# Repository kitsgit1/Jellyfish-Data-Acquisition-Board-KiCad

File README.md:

# Jellyfish Data Acquisition Board KiCad PCB Files
This is one of 3 repositories related to the Jellyfish Data Acquisition project. The goal is to build the hardware for a noninvasive electrode array capable of detecting neronal activity of small jellyfish, the firmware to digitize the signals and control the multiplexing of each pixel, and the software to control the system and graph the data.
| **Hardware** <br/> (You Are Here)      | Firmware      | Software |
| ------------- | ------------- | ------------- |
| <br/>https://github.com/kitsgit1/Jellyfish-Data-Acquisition-Board-KiCad |  <br/>https://github.com/kitsgit1/Jellyfish-Data-Acquisition-STM32 |  <br/>https://github.com/kitsgit1/Jellyfish-Data-Display-GUI |

# Hardware Documentation - Rev A
There are two boards that make up the assembly: the Electrode board and the Digitizer board.
## Jellyfish Electrode Board
The electrode board is responsible for interfacing with the jellyfish and multiplexing all pixels down to one wire using low charge-injection analog mux's. There is an optional path for a front-end buffer amplifier (non-inverting x2 gain for Rf = Rg). I/O consists of the Guard signal which drives the saltwater bath to the same potential as the op-amp reference voltage, the digital I/O to control the shift registers that select the correct pixel through setting all the multiplexers, and the single analog switched electrode signal.

## Jellyfish Digitizer Board
The digitizer board further amplifies the tiny signal from the electrode board into something the STM32's 10MHz/12-bit ADC can handle. The STM32 is also responsible for collecting, storing, and sending data to either the PC over USB or to an SD card.

Details to come...

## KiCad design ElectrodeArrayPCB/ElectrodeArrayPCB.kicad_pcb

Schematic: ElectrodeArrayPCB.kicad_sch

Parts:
BT1: XT30PW-M30.G.Y; AMASS_XT30PW-M_1x02_P2.50mm_Horizontal; LCSC C431092
C1, C6, C7, C8, C9, C13, C14, C15, C18, C20, C22, C23, C24, C25, C30, C36, C38, C39, C41, C42, C43, C46, C51, C52, C53, C54, C55, C56, C59, C63, C64, C68, C70, C72, C73: 100nF; C_0402; Voltage Rated 50V; Tolerance ±10%; Part CL05B104KB54PNC; LCSC C307331
C2, C4, C5, C17, C21, C26, C29, C32, C76: 10uF; C_0805; Voltage Rated 25V; Tolerance ±10%; Part CL21A106KAYNNNE; LCSC C15850
C3, C27, C58, C81: 4.7uF; C_0402; Voltage Rated 10V; Tolerance ±20%; Part CL05A475MP5NRNC; LCSC C23733
C10, C11, C12, C16, C28, C67, C69, C71, C77, C79, C80: 47uF; C_1206; Voltage Rated 10V; Tolerance ±20%; Part CL31A476MPHNNNE; LCSC C96123
C19, C44, C45, C78: 10pF; C_0402; Voltage Rated 50V; Tolerance ±5%; Part CL05C100JB5NNNC; LCSC C32949
C31, C37, C40, C57, C60: 1uF; C_0402; Voltage Rated 25V; Tolerance ±10%; Part CL05A105KA5NQNC; LCSC C52923
C61, C62: 2.2uF; C_0603; Voltage Rated 16V; Tolerance ±10%; Part CL10A225KO8NNNC; LCSC C23630
C65, C66: 470pF; C_0402; Voltage Rated 50V; Tolerance ±10%; Part 0402B471K500NT; LCSC C1537
C74, C75: 20pF; C_0402; Voltage Rated 50V; Tolerance ±5%; Part 0402CG200J500NT; LCSC C1554
D1, D2, D3: Red; D_0603; Part KT-0603R; LCSC C2286
FB1, FB2, FB3, FB4: FB_0805; Current Rating 800mA; Tolerance ±25%; Part GZ2012D101TF; LCSC C1015
J1: HX PZ1.27-2x5P TP; PinHeader_2x05_P1.27mm_Vertical_SMD
J2, J10: Conn_01x10_Pin; Electrode_Line_8_Test
J3, J7, J8, J9, J11: KH-SMAK-SMT; SMA_Wurth_60312102114405_Vertical
J4: 1040310811; microSD_HC_Molex_104031-0811; LCSC C585350
J5: Conn_ARM_SWD_TagConnect_TC2030; Tag-Connect_TC2030-IDC-FP_2x03_P1.27mm_Vertical
J6: Connector, USB-TYPE-C-16P; TYPE-C-SMD_HX-TYPE-C-16PIN; LCSC C2927039
J12: 2.54-1*3PPin; PinHeader_1x03_P2.54mm_Vertical; LCSC C49257
P1, P2: Jumper Shunt; LCSC C2758458
R1, R7, R19, R22, R32, R36, R47, R89, R97, R98, R99, R105: 1kΩ; R_0402; Overload Voltage (Max) 50V; Tolerance ±1%; Part 0402WGF1001TCE; LCSC C11702
R2, R5, R29, R49, R54, R119: 270kΩ; R_0603; Overload Voltage (Max) 75V; Tolerance ±1%; Part 0603WAF2703T5E; LCSC C22965
R3, R42, R46, R90, R91, R118: 100kΩ; R_0402; Overload Voltage (Max) 50V; Tolerance ±1%; Part 0402WGF1003TCE; LCSC C25741
R4, R34, R103: 10kΩ; R_0402; Overload Voltage (Max) 50V; Tolerance ±1%; Part 0402WGF1002TCE; LCSC C25744
R6, R25, R50: 12kΩ; R_0402; Overload Voltage (Max) 50V; Tolerance ±1%; Part 0402WGF1202TCE; LCSC C25752
R8, R51, R102: 0Ω; R_1206; Overload Voltage (Max) 200V; Tolerance ±1%; Part 1206W4F0000T5E; LCSC C17888
R9, R48: 22kΩ; R_0402; Overload Voltage (Max) 50V; Tolerance ±1%; Part 0402WGF2202TCE; LCSC C25768
R10, R11, R17, R18, R20, R21, R23, R27, R28, R30, R31, R35, R37, R44, R45, R53, R55, R58, R71, R78, R85, R86, R87, R88, R92, R95, R107, R109, R110, R111, R113, R114, R115, R120: 0Ω; R_0402; Overload Voltage (Max) 50V; Tolerance ±1%; Part 0402WGF0000TCE; LCSC C17168
R12: 33kΩ; R_0402; Overload Voltage (Max) 50V; Tolerance ±1%; Part 0402WGF3302TCE; LCSC C25779
R13, R100, R106: 49.9Ω; R_0402; Overload Voltage (Max) 50V; Tolerance ±1%; Part 0402WGF499JTCE; LCSC C25120
R14, R26: 100Ω; R_0402; Overload Voltage (Max) 50V; Tolerance ±1%; Part 0402WGF1000TCE; LCSC C25076
R15, R16, R24, R43, R52, R56, R57, R96, R101, R116, R117: 0Ω; R_0402; Overload Voltage (Max) 50V; Tolerance ±1%; Part 0402WGF0000TCE; LCSC C17168; not fitted
R33, R39: 470kΩ; R_0402; Overload Voltage (Max) 50V; Tolerance ±1%; Part 0402WGF4703TCE; LCSC C25790
R38: 220kΩ; R_0402; Overload Voltage (Max) 50V; Tolerance ±1%; Part 0402WGF2203TCE; LCSC C25767
R40, R93: 1MΩ; R_0402; Overload Voltage (Max) 50V; Tolerance ±1%; Part 0402WGF1004TCE; LCSC C26083
R41, R59, R60, R61, R62, R63, R64: 47kΩ; R_0402; Overload Voltage (Max) 50V; Tolerance ±1%; Part 0402WGF4702TCE; LCSC C25792
R65, R66, R67, R68, R69, R70, R72, R73, R74, R75, R76, R77, R79, R80, R81, R82, R83, R84: 10Ω; R_0402; Overload Voltage (Max) 50V; Tolerance ±1%; Part 0402WGF100JTCE; LCSC C25077
R94, R104: 5.1kΩ; R_0603; Overload Voltage (Max) 75V; Tolerance ±1%; Part 0603WAF5101T5E; LCSC C23186
R108: 1Ω; R_0402; Overload Voltage (Max) 50V; Tolerance ±1%; Part 0402WGF100KTCE; LCSC C25086
R112: 0Ω; R_0805; Overload Voltage (Max) 150V; Tolerance ±1%; Part 0805W8F0000T5E; LCSC C17477
S1: Tactile Button, 160gf; SW_TS-1088-AR02016; Voltage Rating (Dc) 12V; Part TS-1088-AR02016; LCSC C720477
TP1, TP2, TP5, TP6, TP7: RH-5000; TestPoint_Loop_D2.54mm_Drill1.5mm_Beaded; LCSC C5277086
TP3: RH-5001; TestPoint_Loop_D2.54mm_Drill1.5mm_Beaded
TP4, TP8, TP9, TP10, TP11, TP12, TP13, TP14: RH-5001; TestPoint_Loop_D2.54mm_Drill1.5mm_Beaded; LCSC C5199801
U1, U4, U28: TPS7A9401DSCR; VSON-10-1EP_3x3mm_P0.5mm_EP1.65x2.4mm_ThermalVias; LCSC C5220127
U2, U3: HX PZ2.54-3x3P ZZ; PinHeader_03x03_0.1in; LCSC C32713290
U5: 74HC4067PW,118; SSOP-24_5.3x8.2mm_P0.65mm; LCSC C179326
U9: CJ431; SOT-23-3_L2.9-W1.6-P1.90-LS2.8-BR; Output Voltage 2.5V~36V; Tolerance ±0.5%; Part CJ431; LCSC C3113
U10: REF2033AIDDCR; SOT-23-5; LCSC C440747
U11: LMP7721; SOIC-8_3.9x4.9mm_P1.27mm
U12: LMP7715; SOT-23-5
U14: ADA4940-1ACPZ-R2; LFCSP-16-1EP_3x3mm_P0.5mm_EP1.3x1.3mm_ThermalVias; LCSC C654337
U15: STM32H7B0VBT6; LQFP-100_14x14mm_P0.5mm; LCSC C730227
U16, U17: OPA847IDBVR; SOT-23-6; LCSC C160422
U19: TMUX1108PW; TSSOP-16_4.4x5mm_P0.65mm
U24, U25: APS6404L-3SQR-SN; SOIC-8_3.9x4.9mm_P1.27mm; LCSC C5333729
U27: REF5025AIDR; SOIC-8_L4.9-W3.9-P1.27-LS6.0-BL
X1: X322516MLB4SI; OSC-SMD_4P-L3.2-W2.5-BL; Frequency Tolerance ±10ppm; Part X322516MLB4SI; LCSC C13738

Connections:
+3.3V: R8.2, R52.2, R112.1
+3.3VA: FB2.2, R51.2
+5V: C9.1, C16.1, R14.2, R18.1, R19.1, R27.2, R30.2, R37.2, R44.1, R45.1, R85.2, R102.2, R109.2, U3.1
/MCU_VDD33: C51.1, C52.1, C53.1, C54.1, C55.1, C56.1, C57.1, C58.1, R58.1, R71.1, R78.1, R89.1, R92.2, R112.2, U15.6 (VBAT), U15.11 (VDD), U15.27 (VDD), U15.50 (VDD), U15.75 (VDD), U15.100 (VDD)
/PA11_USB_DM: J6.A7 (D-), J6.B7 (D-), U15.70 (PA11)
/PA12_USB_DP: J6.A6 (D+), J6.B6 (D+), U15.71 (PA12)
/USART1_RX: J12.2, U15.54 (PB15)
/USART1_TX: J12.1, U15.53 (PB14)
/amp_inverting_input: R34.1, U12.3 (+)
/battery: BT1.1 (+), C20.1, C21.1, FB1.1, FB3.1, FB4.1
/grd_drv_out: R26.2, U12.1, U12.4 (-)
/ldo_3v3: C10.1, C17.1, C18.1, R5.2, R8.1, TP2.1, U1.8 (SNS), U1.9 (OUT), U1.10 (OUT)
/ldo_3v3A: C28.1, C29.1, C30.1, R49.2, R51.1, TP7.1, U4.8 (SNS), U4.9 (OUT), U4.10 (OUT)
/ldo_5v: C4.1, C7.1, C80.1, R54.2, R102.1, TP1.1, U28.8 (SNS), U28.9 (OUT), U28.10 (OUT)
/vbat_post_fb5: C5.1, C6.1, FB3.2, R1.2, R119.1, U28.1 (IN), U28.2 (IN)
/vbat_post_fb33: C1.1, C2.1, FB1.2, R2.1, R7.1, U1.1 (IN), U1.2 (IN)
/vbat_post_fb33A: C22.1, C26.1, FB4.2, R29.1, R47.1, U4.1 (IN), U4.2 (IN)
ADC_N: R100.2, R114.1
ADC_P: R106.2, R113.1
GND: BT1.2 (-), C1.2, C2.2, C3.2, C4.2, C5.2, C6.2, C7.2, C8.2, C9.2, C10.2, C11.2, C12.2, C13.2, C14.2, C15.2, C16.2, C17.2, C18.2, C19.1, C20.2, C21.2, C22.2, C23.2, C24.2, C25.2, C26.2, C27.2, C28.2, C29.2, C30.2, C31.2, C32.2, C36.2, C37.2, C38.2, C39.2, C40.2, C41.2, C42.1, C43.2, C44.2, C45.1, C46.2, C51.2, C52.2, C53.2, C54.2, C55.2, C56.2, C57.2, C58.2, C59.2, C60.2, C61.2, C62.2, C63.2, C64.2, C68.2, C69.2, C70.2, C71.2, C72.2, C73.2, C76.2, C77.2, C79.2, C80.2, C81.2, J3.2 (Ext), J4.6 (VSS), J4.9 (SHIELD), J5.5 (GND), J6.A12B1 (GND), J6.B12A1 (GND), J7.2 (Ext), J8.2 (Ext), J9.2 (Ext), J11.2 (Ext), J12.3, R3.2, R6.2, R9.2, R12.2, R13.2, R15.2, R17.1, R24.1, R25.2, R46.2, R48.2, R50.2, R93.2, R94.2, R104.2, R107.2, R108.2, R116.1, R117.2, R118.2, S1.1 (A), TP3.1, TP4.1, TP8.1, TP9.1, TP10.1, TP11.1, U1.6 (GND), U1.11 (EPAD), U2.1, U2.3, U2.7, U2.9, U3.2, U3.4, U3.5, U4.6 (GND), U4.11 (EPAD), U5.12 (GND), U5.13 (S3), U5.15 (~E), U9.3 (AN), U10.2 (GND), U11.3 (V-), U12.2 (V-), U14.13 (-Vs), U14.14 (-Vs), U14.15 (-Vs), U14.16 (-Vs), U14.17 (EP), U15.10 (VSS), U15.19 (VSSA), U15.26 (VSS), U15.49 (VSS), U15.74 (VSS), U15.99 (VSS), U16.2 (V-), U17.2 (V-), U19.3 (VSS), U19.14 (GND), U24.4 (VSS), U25.4 (VSS), U27.4 (GND), U28.6 (GND), U28.11 (EPAD), X1.2 (GND), X1.4 (GND)
unnamed: C14.1, C67.1, P2.2, R23.1, R53.1, R101.2
unnamed: C41.1, C76.1, R85.1, R95.2, U14.5 (+Vs), U14.6 (+Vs), U14.7 (+Vs), U14.8 (+Vs)
unnamed: C61.1, C62.1, C63.1, C64.1, U15.48 (VCAP), U15.73 (VCAP)
unnamed: C65.2, C66.1, R107.1
unnamed: C67.2, R108.1
unnamed: D1.2, R1.1
unnamed: D2.2, R7.2
unnamed: D3.2, R47.2
unnamed: J1.1, R40.2, R43.2
unnamed: J1.3, R39.2
unnamed: J1.5, R38.2
unnamed: J1.7, R42.2
unnamed: J1.9, P1.1, R41.2
unnamed: J1.2, J1.4, J1.6, J1.8, J1.10, P1.2, R43.1, R55.1, R56.1, R105.1
unnamed: J2.1, U5.9 (I0)
unnamed: J2.2, U5.8 (I1)
unnamed: J2.3, U5.7 (I2)
unnamed: J2.4, U5.6 (I3)
unnamed: J2.5, U5.5 (I4)
unnamed: J2.6, U5.4 (I5)
unnamed: J2.7, U5.3 (I6)
unnamed: J2.8, U5.2 (I7)
unnamed: J2.9, J8.1 (In)
unnamed: J3.1 (In), R20.1
unnamed: J4.5 (CLK), R64.2, R69.2
unnamed: J4.3 (CMD), R63.2, R70.2
unnamed: J4.7 (DAT0), R60.2, R65.2
unnamed: J4.8 (DAT1), R61.2, R66.2
unnamed: J4.1 (DAT2), R59.2, R67.2
unnamed: J4.2 (DAT3/CD), R62.2, R68.2
unnamed: C36.1, J4.4 (VDD), R58.2, R59.1, R60.1, R61.1, R62.1, R63.1, R64.1
unnamed: J5.4 (SWCLK), R87.1
unnamed: J5.2 (SWDIO), R88.2
unnamed: J5.1 (VCC), R91.1, R92.1
unnamed: J5.3 (~RESET), R86.1
unnamed: J6.A5 (CC1), R104.1
unnamed: J6.B5 (CC2), R94.1
unnamed: C46.1, J6.S1 (SHIELD), R93.1
unnamed: J6.A9B4 (VBUS), J6.B9A4 (VBUS), R96.1
unnamed: J7.1 (In), R120.2
unnamed: C19.2, J9.1 (In), R10.2, R11.2
unnamed: J10.1, U19.4 (S1)
unnamed: J10.2, U19.5 (S2)
unnamed: J10.3, U19.6 (S3)
unnamed: J10.4, U19.7 (S4)
unnamed: J10.5, U19.9 (S8)
unnamed: J10.6, U19.10 (S7)
unnamed: J10.7, U19.11 (S6)
unnamed: J10.8, U19.12 (S5)
unnamed: J2.10, J10.9
unnamed: J10.10, R13.1
unnamed: J11.1 (In), R28.2
unnamed: R21.2, U2.5
unnamed: R28.1, R55.2, U17.1
unnamed: R56.2, R57.1
unnamed: R17.2, R52.1, R103.1
unnamed: R33.2, R35.2, R57.2, R115.1
unnamed: R115.2, U16.1
unnamed: C42.2, R90.1, S1.2 (B)
unnamed: R2.2, R3.1, U1.3 (EN_UV)
unnamed: R5.1, R6.1, U1.5 (FB_PG)
unnamed: C3.1, R9.1, U1.7 (NR/SS)
unnamed: D2.1, U1.4 (PG)
unnamed: R29.2, R46.1, U4.3 (EN_UV)
unnamed: R49.1, R50.1, U4.5 (FB_PG)
unnamed: C27.1, R48.1, U4.7 (NR/SS)
unnamed: D3.1, U4.4 (PG)
unnamed: R10.1, U5.1 (COM)
unnamed: C8.1, R44.2, U5.24 (VCC)
unnamed: R16.1, R19.2, R101.1, U9.2 (CAT)
unnamed: R15.1, R16.2, U9.1 (REF)
unnamed: C70.1, C71.1, R109.1, U10.3 (EN), U10.4 (IN)
unnamed: C72.1, R110.1, U10.1 (Vbias)
unnamed: C73.1, R111.1, U10.5 (Vref)
unnamed: R20.2, U11.1 (IN+)
unnamed: C78.1, R4.1, R22.1, R34.2, U11.8 (IN-)
unnamed: C11.1, C12.1, C13.1, R27.1, U11.6 (V+)
unnamed: C78.2, R4.2, R31.2, U11.4 (Vout)
unnamed: C15.1, C77.1, C79.1, R14.1, U12.5 (V+)
unnamed: C74.2, R99.2, U14.4 (+FB)
unnamed: C75.1, R97.1, R105.2, U14.2 (+IN)
unnamed: R113.2, U14.10 (+OUT)
unnamed: C75.2, R97.2, U14.1 (-FB)
unnamed: C74.1, R98.2, R99.1, U14.3 (-IN)
unnamed: R114.2, U14.11 (-OUT)
unnamed: R110.2, U14.9 (VOCM)
unnamed: R95.1, U14.12 (~DISABLE)
unnamed: R103.2, U15.94 (BOOT0)
unnamed: R96.2, U15.68 (PA9)
unnamed: R88.1, R91.2, U15.72 (PA13)
unnamed: R87.2, U15.76 (PA14)
unnamed: C65.1, R100.1, U15.17 (PC2_C)
unnamed: C66.2, R106.1, U15.18 (PC3_C)
unnamed: R65.1, U15.65 (PC8)
unnamed: R66.1, U15.66 (PC9)
unnamed: R67.1, U15.78 (PC10)
unnamed: R68.1, U15.79 (PC11)
unnamed: R69.1, U15.80 (PC12)
unnamed: R81.1, U15.58 (PD11)
unnamed: R82.1, U15.59 (PD12)
unnamed: R84.1, U15.60 (PD13)
unnamed: R73.2, U15.37 (PE7)
unnamed: R74.2, U15.38 (PE8)
unnamed: R75.2, U15.39 (PE9)
unnamed: R76.2, U15.40 (PE10)
unnamed: R72.1, R79.1, U15.41 (PE11)
unnamed: C45.2, U15.12 (PH0), X1.3 (OSC)
unnamed: C44.1, U15.13 (PH1), X1.1 (OSC)
unnamed: C59.1, C60.1, FB2.1, U15.21 (VDDA)
unnamed: R21.1, R31.1, R120.1, U16.3 (+)
unnamed: R32.1, R33.1, U16.4 (-)
unnamed: C23.1, R30.1, U16.6 (V+)
unnamed: R116.2, U16.5 (~DIS)
unnamed: R35.1, U17.3 (+)
unnamed: R36.1, R38.1, R39.1, R40.1, R41.1, R42.1, U17.4 (-)
unnamed: C24.1, R37.1, U17.6 (V+)
unnamed: R117.1, U17.5 (~DIS)
unnamed: R11.1, U19.8 (D)
unnamed: C25.1, R45.2, U19.2 (EN), U19.13 (VDD)
unnamed: R77.2, U24.6 (SCLK)
unnamed: R75.1, U24.3 (SIO2)
unnamed: R76.1, U24.7 (SIO3)
unnamed: R73.1, U24.5 (SI/SIO0)
unnamed: R74.1, U24.2 (SO/SIO1)
unnamed: C37.1, C38.1, R71.2, U24.8 (VDD)
unnamed: R72.2, U24.1 (~CE)
unnamed: R80.1, U25.6 (SCLK)
unnamed: R83.2, U25.3 (SIO2)
unnamed: R84.2, U25.7 (SIO3)
unnamed: R81.2, U25.5 (SI/SIO0)
unnamed: R82.2, U25.2 (SO/SIO1)
unnamed: C39.1, C40.1, R78.2, U25.8 (VDD)
unnamed: R79.2, U25.1 (~CE)
unnamed: C31.1, C32.1, U27.5 (Trim/NR)
unnamed: C68.1, C69.1, R18.2, U27.2 (Vin)
unnamed: P2.1, R53.2, U27.6 (Vout)
unnamed: R118.1, R119.2, U28.3 (EN_UV)
unnamed: R25.1, R54.1, U28.5 (FB_PG)
unnamed: C81.1, R12.1, U28.7 (NR/SS)
unnamed: D1.1, U28.4 (PG)
PA7_OCTASPI_P1_IO2: R83.1, U15.31 (PA7)
PB2_OCTASPI_P1_CLK: R77.1, R80.2, U15.36 (PB2)
PD2_SDMMC1_CMD: R70.1, U15.83 (PD2)
STM32_RSTn: C43.1, R86.2, R89.2, R90.2, U15.14 (NRST)
Shift_OEb: U3.3, U15.28 (PA4)
Shift_RCLK: U3.6, U15.29 (PA5)
Shift_SER: U3.7, U15.33 (PC5)
Shift_SRCLK: U3.9, U15.32 (PC4)
Shift_SRCLRb: U3.8, U15.30 (PA6)
VCM_Guard_2.5V: R22.2, R23.2, R24.2, R32.2, R36.2, R98.1, TP5.1
Vref: R111.2, U15.20 (VREF+)
guard_ring: R26.1, TP6.1, U2.2, U2.4, U2.6, U2.8, U11.2 (GRD), U11.7 (GRD)
s0: TP14.1, U5.10 (S0), U15.1 (PE2), U19.1 (A0)
s1: TP13.1, U5.11 (S1), U15.2 (PE3), U19.16 (A1)
s2: TP12.1, U5.14 (S2), U15.3 (PE4), U19.15 (A2)

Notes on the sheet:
VCM=2.5V here
Alternate ram possibilities: APS12808L-3OBM-BA (128Mb OSPI, mouser) S70KL1281 (128Mb hyperam/OSPI, obsolete) W956A8MBYA5I (64Mb, LCSC stock, hyperbus) S66/67WVO32M8DALL/BLL (256Mb, OSPI)
16MHz
1.65V CM
1ms per AP spike (really 2-10ms) 20 points per spike -> 50us per sample -> 20kHz sample rate. 64 electrodes -> 1.28MHz sample rate. 4096 electrodes -> 81.92MHz sample rate, single CH. For now, pick ADC for 2MHz. High bit count.
DS Table 23

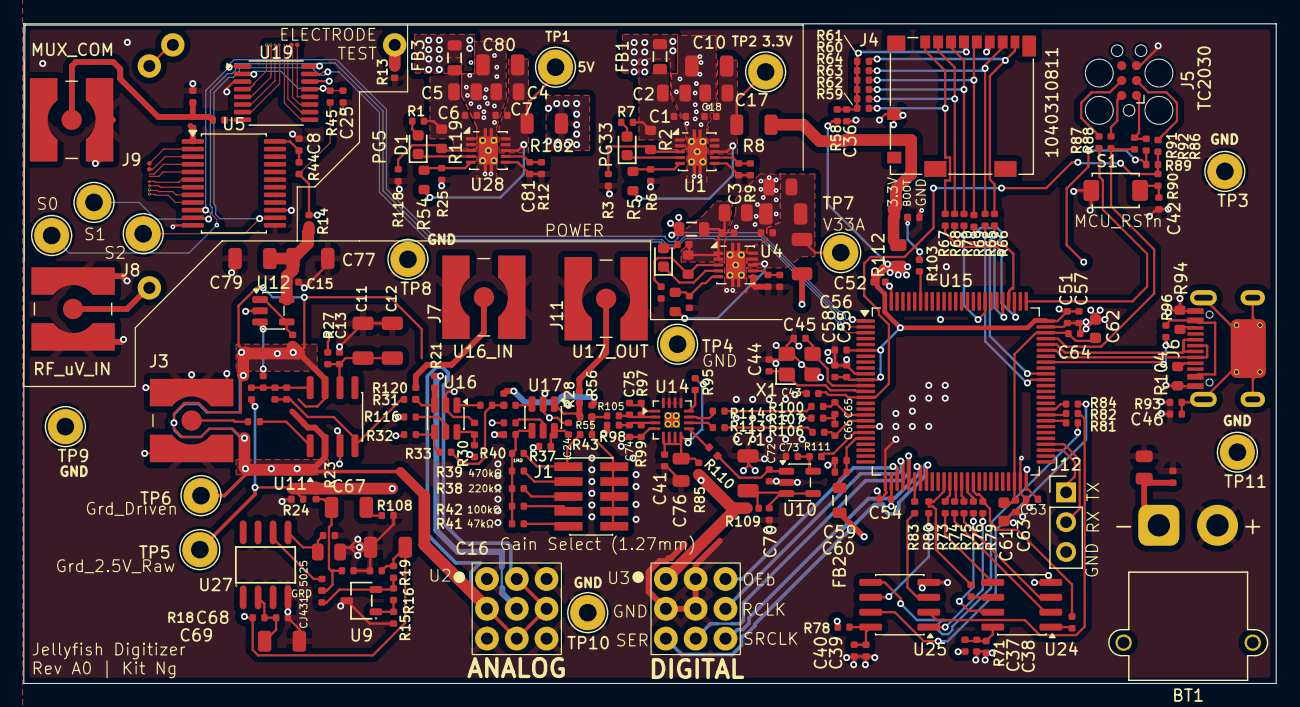
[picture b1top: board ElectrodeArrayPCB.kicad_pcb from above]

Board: 4 copper layers, 106.7 x 56.2 mm, 248 parts (0 on the bottom side), 175 nets.

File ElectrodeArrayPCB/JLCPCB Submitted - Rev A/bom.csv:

Designator,Footprint,Quantity,Value,LCSC Part #
BT1,AMASS_XT30PW-M_1x02_P2.50mm_Horizontal,1,XT30PW-M30.G.Y,C431092
"C1, C13, C14, C15, C18, C20, C22, C23, C24, C25, C30, C36, C38, C39, C41, C42, C43, C46, C51, C52, C53, C54, C55, C56, C59, C6, C63, C64, C68, C7, C70, C72, C73, C8, C9",C_0402,35,100nF,C307331
"C10, C11, C12, C16, C28, C67, C69, C71, C77, C79, C80",C_1206,11,47uF,C96123
"C17, C2, C21, C26, C29, C32, C4, C5, C76",C_0805,9,10uF,C15850
"C19, C44, C45, C78",C_0402,4,10pF,C32949
"C27, C3, C58, C81",C_0402,4,4.7uF,C23733
"C31, C37, C40, C57, C60",C_0402,5,1uF,C52923
"C61, C62",C_0603,2,2.2uF,C23630
"C65, C66",C_0402,2,470pF,C1537
"C74, C75",C_0402,2,20pF,C1554
"D1, D2, D3",D_0603,3,Red,C2286
"FB1, FB2, FB3, FB4",FB_0805,4,~,C1015
J1,PinHeader_2x05_P1.27mm_Vertical_SMD,1,HX PZ1.27-2x5P TP,
"J11, J3, J7, J8, J9",SMA_Wurth_60312102114405_Vertical,5,KH-SMAK-SMT,
J12,PinHeader_1x03_P2.54mm_Vertical,1,2.54-1*3PPin,C49257
J4,microSD_HC_Molex_104031-0811,1,1040310811,C585350
J6,TYPE-C-SMD_HX-TYPE-C-16PIN,1,"Connector, USB-TYPE-C-16P",C2927039
"R1, R105, R19, R22, R32, R36, R47, R7, R89, R97, R98, R99",R_0402,12,1kΩ,C11702
"R10, R101, R107, R109, R11, R110, R111, R113, R114, R115, R116, R117, R120, R15, R16, R17, R18, R20, R21, R23, R24, R27, R28, R30, R31, R35, R37, R43, R44, R45, R52, R53, R55, R56, R57, R58, R71, R78, R85, R86, R87, R88, R92, R95, R96",R_0402,45,0Ω,C17168
"R100, R106, R13",R_0402,3,49.9Ω,C25120
"R102, R51, R8",R_1206,3,0Ω,C17888
"R103, R34, R4",R_0402,3,10kΩ,C25744
"R104, R94",R_0603,2,5.1kΩ,C23186
R108,R_0402,1,1Ω,C25086
R112,R_0805,1,0Ω,C17477
"R118, R3, R42, R46, R90, R91",R_0402,6,100kΩ,C25741
"R119, R2, R29, R49, R5, R54",R_0603,6,270kΩ,C22965
R12,R_0402,1,33kΩ,C25779
"R14, R26",R_0402,2,100Ω,C25076
"R25, R50, R6",R_0402,3,12kΩ,C25752
"R33, R39",R_0402,2,470kΩ,C25790
R38,R_0402,1,220kΩ,C25767
"R40, R93",R_0402,2,1MΩ,C26083
"R41, R59, R60, R61, R62, R63, R64",R_0402,7,47kΩ,C25792
"R48, R9",R_0402,2,22kΩ,C25768
"R65, R66, R67, R68, R69, R70, R72, R73, R74, R75, R76, R77, R79, R80, R81, R82, R83, R84",R_0402,18,10Ω,C25077
S1,SW_TS-1088-AR02016,1,"Tactile Button, 160gf",C720477
"TP1, TP2, TP5, TP6, TP7",TestPoint_Loop_D2.54mm_Drill1.5mm_Beaded,5,RH-5000,C5277086
"TP10, TP11, TP12, TP13, TP14, TP4, TP8, TP9",TestPoint_Loop_D2.54mm_Drill1.5mm_Beaded,8,RH-5001,C5199801
TP3,TestPoint_Loop_D2.54mm_Drill1.5mm_Beaded,1,RH-5001,
"U1, U28, U4",VSON-10-1EP_3x3mm_P0.5mm_EP1.65x2.4mm_ThermalVias,3,TPS7A9401DSCR,C5220127
U10,SOT-23-5,1,REF2033AIDDCR,C440747
U11,SOIC-8_3.9x4.9mm_P1.27mm,1,LMP7721,
U12,SOT-23-5,1,LMP7715,
U14,LFCSP-16-1EP_3x3mm_P0.5mm_EP1.3x1.3mm_ThermalVias,1,ADA4940-1ACPZ-R2,C654337
U15,LQFP-100_14x14mm_P0.5mm,1,STM32H7B0VBT6,C730227
"U16, U17",SOT-23-6,2,OPA847IDBVR,C160422
U19,TSSOP-16_4.4x5mm_P0.65mm,1,TMUX1108PW,
"U2, U3",PinHeader_03x03_0.1in,2,HX PZ2.54-3x3P ZZ,C32713290
"U24, U25",SOIC-8_3.9x4.9mm_P1.27mm,2,APS6404L-3SQR-SN,C5333729
U27,SOIC-8_L4.9-W3.9-P1.27-LS6.0-BL,1,REF5025AIDR,
U5,SSOP-24_5.3x8.2mm_P0.65mm,1,"74HC4067PW,118",C179326
U9,SOT-23-3_L2.9-W1.6-P1.90-LS2.8-BR,1,CJ431,C3113
X1,OSC-SMD_4P-L3.2-W2.5-BL,1,X322516MLB4SI,C13738

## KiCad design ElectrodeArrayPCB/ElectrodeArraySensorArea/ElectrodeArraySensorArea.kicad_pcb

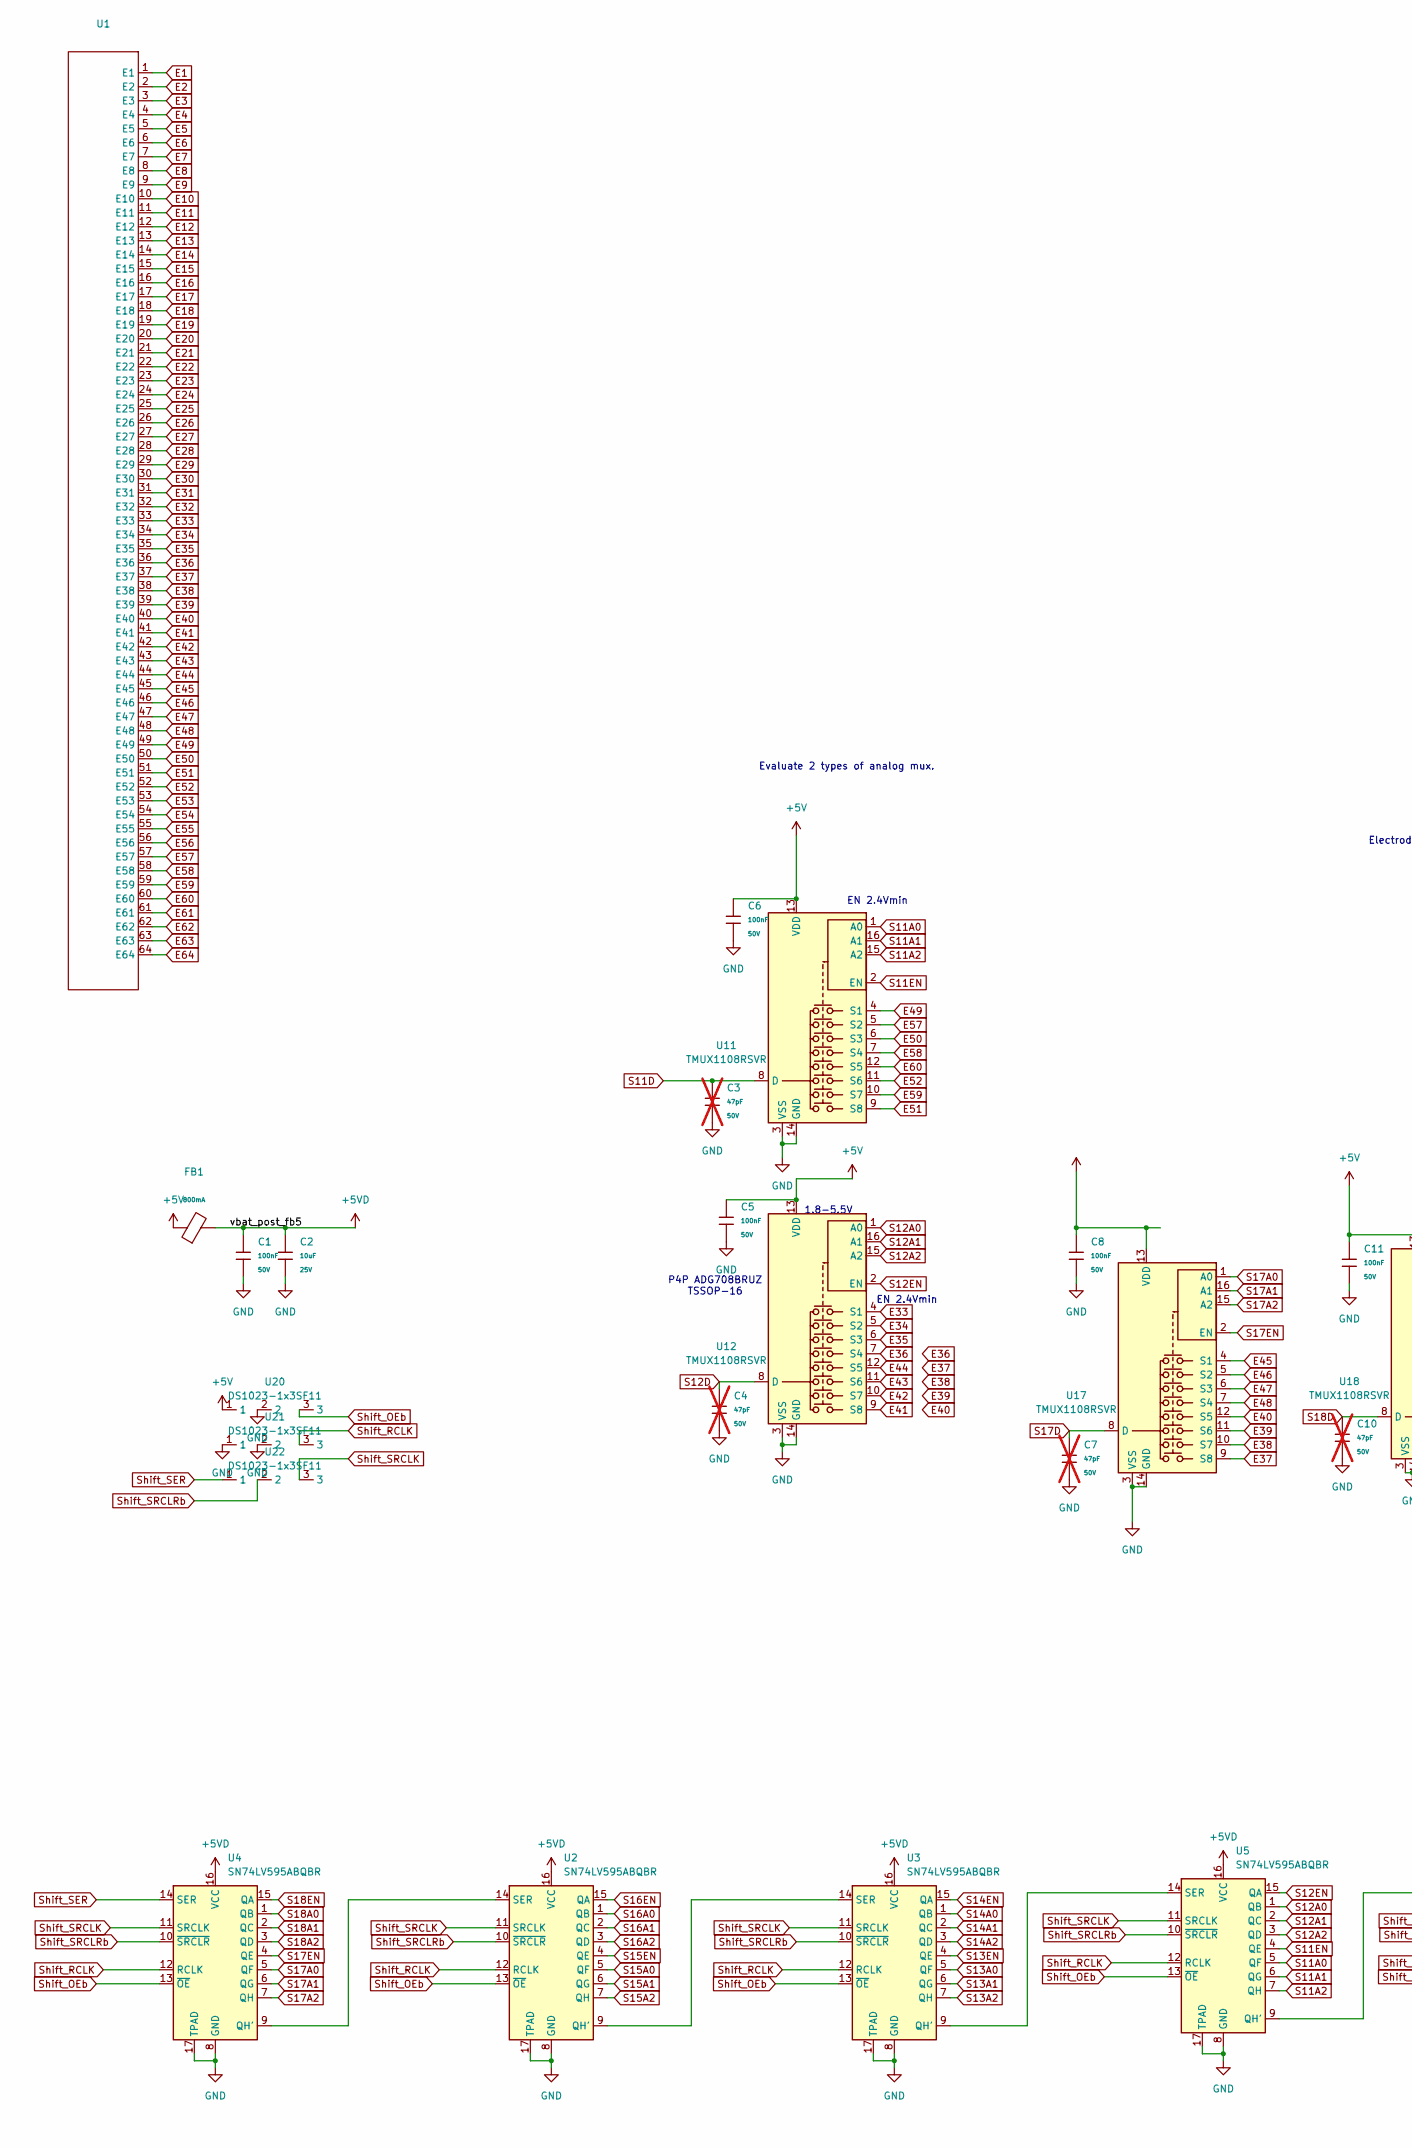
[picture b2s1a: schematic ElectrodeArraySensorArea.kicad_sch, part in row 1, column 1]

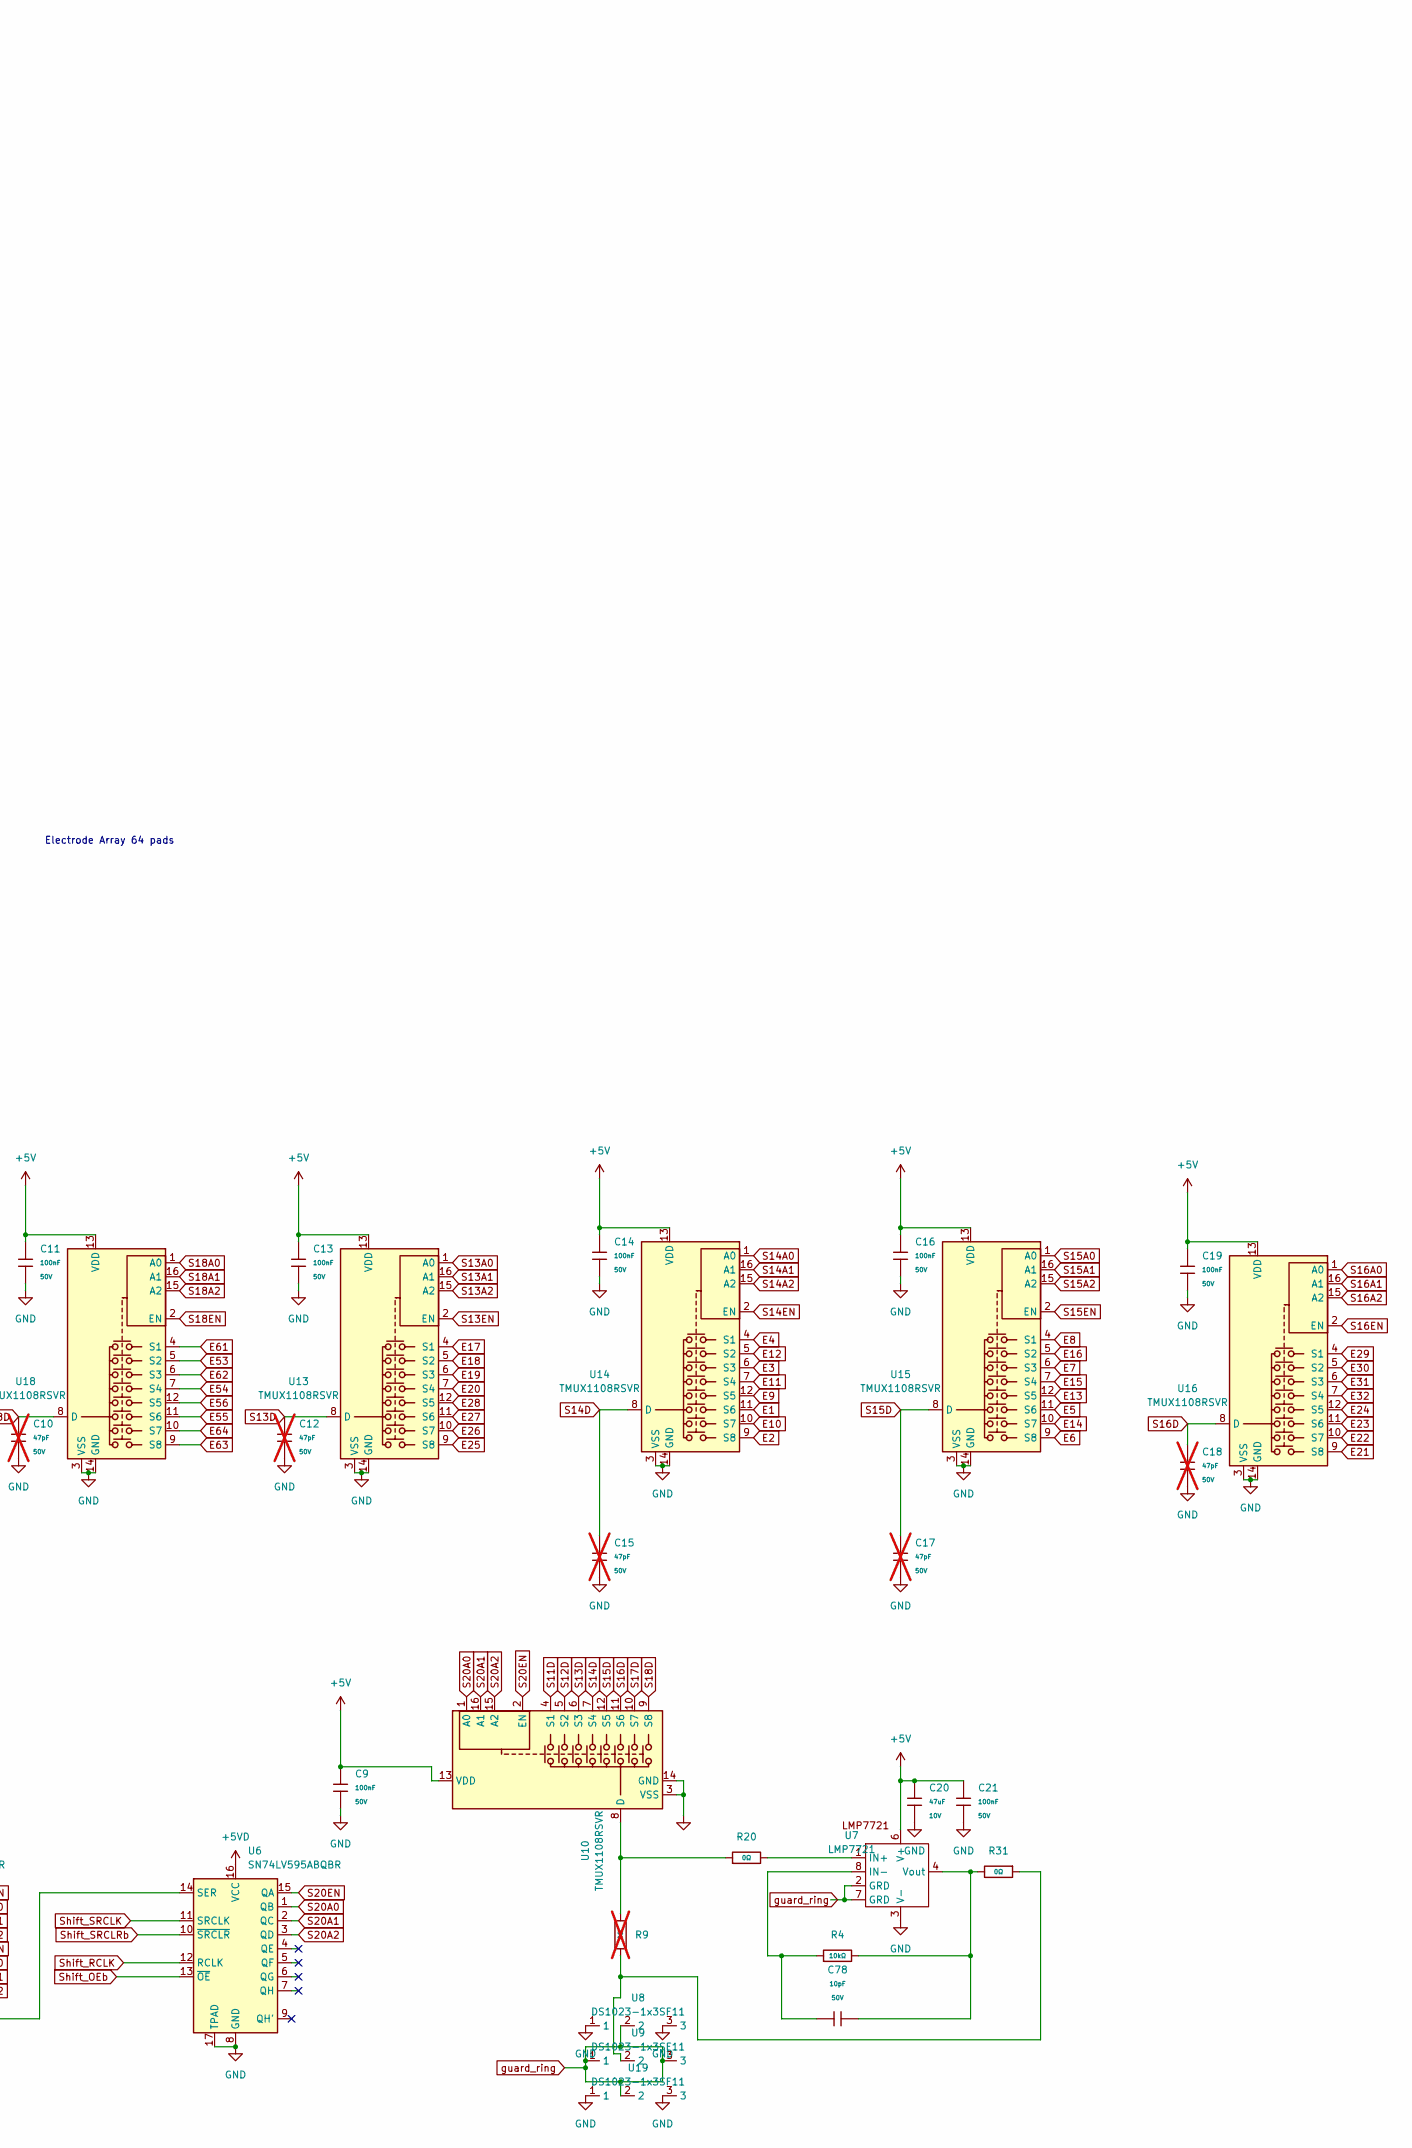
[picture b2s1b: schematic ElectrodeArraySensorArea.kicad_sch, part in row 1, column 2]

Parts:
C1, C5, C6, C8, C9, C11, C13, C14, C16, C19, C21: 100nF; C_0402; Voltage Rated 50V; Tolerance ±10%; Part CL05B104KB54PNC; LCSC C307331
C2: 10uF; C_0805; Voltage Rated 25V; Tolerance ±10%; Part CL21A106KAYNNNE; LCSC C15850
C3, C4, C7, C10, C12, C15, C17, C18: 47pF; C_0402; Voltage Rated 50V; Tolerance ±5%; Part 0402CG470J500NT; LCSC C1567; not fitted
C20: 47uF; C_1206; Voltage Rated 10V; Tolerance ±20%; Part CL31A476MPHNNNE; LCSC C96123
C78: 10pF; C_0402; Voltage Rated 50V; Tolerance ±5%; Part CL05C100JB5NNNC; LCSC C32949
FB1: FB_0805; Current Rating 800mA; Tolerance ±25%; Part GZ2012D101TF; LCSC C1015
R4: 10kΩ; R_0402; Overload Voltage (Max) 50V; Tolerance ±1%; Part 0402WGF1002TCE; LCSC C25744
R9: 0Ω; R_0402; Overload Voltage (Max) 50V; Tolerance ±1%; Part 0402WGF0000TCE; LCSC C17168; not fitted
R20, R31: 0Ω; R_0402; Overload Voltage (Max) 50V; Tolerance ±1%; Part 0402WGF0000TCE; LCSC C17168
U1: Electrode_Array_64_Square
U2, U3, U4, U5, U6: SN74LV595ABQBR; DHVQFN-16-1EP_2.5x3.5mm_P0.5mm_EP1x2mm; LCSC C7083313
U7: LMP7721; SOIC-8_3.9x4.9mm_P1.27mm
U8, U9, U19, U20, U21, U22: DS1023-1x3SF11; PinHeader_1x03_P2.54mm_Vertical; LCSC C7509516
U10, U11, U12, U13, U14, U15, U16, U17, U18: TMUX1108RSVR; UQFN-16_1.8x2.6mm_P0.4mm

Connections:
+5V: C5.1, C6.1, C8.1, C9.1, C11.1, C13.1, C14.1, C16.1, C19.1, C20.1, C21.1, FB1.1, U7.6 (V+), U10.13 (VDD), U11.13 (VDD), U12.13 (VDD), U13.13 (VDD), U14.13 (VDD), U15.13 (VDD), U16.13 (VDD), U17.13 (VDD), U18.13 (VDD), U20.1
+5VD: C1.1, C2.1, FB1.2, U2.16 (VCC), U3.16 (VCC), U4.16 (VCC), U5.16 (VCC), U6.16 (VCC)
E1: U1.1 (E1), U14.11 (S6)
E2: U1.2 (E2), U14.9 (S8)
E3: U1.3 (E3), U14.6 (S3)
E4: U1.4 (E4), U14.4 (S1)
E5: U1.5 (E5), U15.11 (S6)
E6: U1.6 (E6), U15.9 (S8)
E7: U1.7 (E7), U15.6 (S3)
E8: U1.8 (E8), U15.4 (S1)
E9: U1.9 (E9), U14.12 (S5)
E10: U1.10 (E10), U14.10 (S7)
E11: U1.11 (E11), U14.7 (S4)
E12: U1.12 (E12), U14.5 (S2)
E13: U1.13 (E13), U15.12 (S5)
E14: U1.14 (E14), U15.10 (S7)
E15: U1.15 (E15), U15.7 (S4)
E16: U1.16 (E16), U15.5 (S2)
E17: U1.17 (E17), U13.4 (S1)
E18: U1.18 (E18), U13.5 (S2)
E19: U1.19 (E19), U13.6 (S3)
E20: U1.20 (E20), U13.7 (S4)
E21: U1.21 (E21), U16.9 (S8)
E22: U1.22 (E22), U16.10 (S7)
E23: U1.23 (E23), U16.11 (S6)
E24: U1.24 (E24), U16.12 (S5)
E25: U1.25 (E25), U13.9 (S8)
E26: U1.26 (E26), U13.10 (S7)
E27: U1.27 (E27), U13.11 (S6)
E28: U1.28 (E28), U13.12 (S5)
E29: U1.29 (E29), U16.4 (S1)
E30: U1.30 (E30), U16.5 (S2)
E31: U1.31 (E31), U16.6 (S3)
E32: U1.32 (E32), U16.7 (S4)
E33: U1.33 (E33), U12.4 (S1)
E34: U1.34 (E34), U12.5 (S2)
E35: U1.35 (E35), U12.6 (S3)
E36: U1.36 (E36), U12.7 (S4)
E37: U1.37 (E37), U17.9 (S8)
E38: U1.38 (E38), U17.10 (S7)
E39: U1.39 (E39), U17.11 (S6)
E40: U1.40 (E40), U17.12 (S5)
E41: U1.41 (E41), U12.9 (S8)
E42: U1.42 (E42), U12.10 (S7)
E43: U1.43 (E43), U12.11 (S6)
E44: U1.44 (E44), U12.12 (S5)
E45: U1.45 (E45), U17.4 (S1)
E46: U1.46 (E46), U17.5 (S2)
E47: U1.47 (E47), U17.6 (S3)
E48: U1.48 (E48), U17.7 (S4)
E49: U1.49 (E49), U11.4 (S1)
E50: U1.50 (E50), U11.6 (S3)
E51: U1.51 (E51), U11.9 (S8)
E52: U1.52 (E52), U11.11 (S6)
E53: U1.53 (E53), U18.5 (S2)
E54: U1.54 (E54), U18.7 (S4)
E55: U1.55 (E55), U18.11 (S6)
E56: U1.56 (E56), U18.12 (S5)
E57: U1.57 (E57), U11.5 (S2)
E58: U1.58 (E58), U11.7 (S4)
E59: U1.59 (E59), U11.10 (S7)
E60: U1.60 (E60), U11.12 (S5)
E61: U1.61 (E61), U18.4 (S1)
E62: U1.62 (E62), U18.6 (S3)
E63: U1.63 (E63), U18.9 (S8)
E64: U1.64 (E64), U18.10 (S7)
GND: C1.2, C2.2, C3.2, C4.2, C5.2, C6.2, C7.2, C8.2, C9.2, C10.2, C11.2, C12.2, C13.2, C14.2, C15.2, C16.2, C17.2, C18.2, C19.2, C20.2, C21.2, U2.8 (GND), U2.17 (TPAD), U3.8 (GND), U3.17 (TPAD), U4.8 (GND), U4.17 (TPAD), U5.8 (GND), U5.17 (TPAD), U6.8 (GND), U6.17 (TPAD), U7.3 (V-), U8.1, U8.3, U10.3 (VSS), U10.14 (GND), U11.3 (VSS), U11.14 (GND), U12.3 (VSS), U12.14 (GND), U13.3 (VSS), U13.14 (GND), U14.3 (VSS), U14.14 (GND), U15.3 (VSS), U15.14 (GND), U16.3 (VSS), U16.14 (GND), U17.3 (VSS), U17.14 (GND), U18.3 (VSS), U18.14 (GND), U19.1, U19.3, U20.2, U21.1, U21.2
unnamed: R9.1, R31.1, U9.2
unnamed: U2.9 (QH'), U3.14 (SER)
unnamed: U2.14 (SER), U4.9 (QH')
unnamed: U3.9 (QH'), U5.14 (SER)
unnamed: U5.9 (QH'), U6.14 (SER)
unnamed: R20.2, U7.1 (IN+)
unnamed: C78.1, R4.1, U7.8 (IN-)
unnamed: C78.2, R4.2, R31.2, U7.4 (Vout)
unnamed: R9.2, R20.1, U10.8 (D)
S11A0: U5.5 (QF), U11.1 (A0)
S11A1: U5.6 (QG), U11.16 (A1)
S11A2: U5.7 (QH), U11.15 (A2)
S11D: C3.1, U10.4 (S1), U11.8 (D)
S11EN: U5.4 (QE), U11.2 (EN)
S12A0: U5.1 (QB), U12.1 (A0)
S12A1: U5.2 (QC), U12.16 (A1)
S12A2: U5.3 (QD), U12.15 (A2)
S12D: C4.1, U10.5 (S2), U12.8 (D)
S12EN: U5.15 (QA), U12.2 (EN)
S13A0: U3.5 (QF), U13.1 (A0)
S13A1: U3.6 (QG), U13.16 (A1)
S13A2: U3.7 (QH), U13.15 (A2)
S13D: C12.1, U10.6 (S3), U13.8 (D)
S13EN: U3.4 (QE), U13.2 (EN)
S14A0: U3.1 (QB), U14.1 (A0)
S14A1: U3.2 (QC), U14.16 (A1)
S14A2: U3.3 (QD), U14.15 (A2)
S14D: C15.1, U10.7 (S4), U14.8 (D)
S14EN: U3.15 (QA), U14.2 (EN)
S15A0: U2.5 (QF), U15.1 (A0)
S15A1: U2.6 (QG), U15.16 (A1)
S15A2: U2.7 (QH), U15.15 (A2)
S15D: C17.1, U10.12 (S5), U15.8 (D)
S15EN: U2.4 (QE), U15.2 (EN)
S16A0: U2.1 (QB), U16.1 (A0)
S16A1: U2.2 (QC), U16.16 (A1)
S16A2: U2.3 (QD), U16.15 (A2)
S16D: C18.1, U10.11 (S6), U16.8 (D)
S16EN: U2.15 (QA), U16.2 (EN)
S17A0: U4.5 (QF), U17.1 (A0)
S17A1: U4.6 (QG), U17.16 (A1)
S17A2: U4.7 (QH), U17.15 (A2)
S17D: C7.1, U10.10 (S7), U17.8 (D)
S17EN: U4.4 (QE), U17.2 (EN)
S18A0: U4.1 (QB), U18.1 (A0)
S18A1: U4.2 (QC), U18.16 (A1)
S18A2: U4.3 (QD), U18.15 (A2)
S18D: C10.1, U10.9 (S8), U18.8 (D)
S18EN: U4.15 (QA), U18.2 (EN)
S20A0: U6.1 (QB), U10.1 (A0)
S20A1: U6.2 (QC), U10.16 (A1)
S20A2: U6.3 (QD), U10.15 (A2)
S20EN: U6.15 (QA), U10.2 (EN)
Shift_OEb: U2.13 (~OE), U3.13 (~OE), U4.13 (~OE), U5.13 (~OE), U6.13 (~OE), U20.3
Shift_RCLK: U2.12 (RCLK), U3.12 (RCLK), U4.12 (RCLK), U5.12 (RCLK), U6.12 (RCLK), U21.3
Shift_SER: U4.14 (SER), U22.1
Shift_SRCLK: U2.11 (SRCLK), U3.11 (SRCLK), U4.11 (SRCLK), U5.11 (SRCLK), U6.11 (SRCLK), U22.3
Shift_SRCLRb: U2.10 (~SRCLR), U3.10 (~SRCLR), U4.10 (~SRCLR), U5.10 (~SRCLR), U6.10 (~SRCLR), U22.2
guard_ring: U7.2 (GRD), U7.7 (GRD), U8.2, U9.1, U9.3, U19.2

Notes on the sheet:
P4P ADG708BRUZ TSSOP-16
EN 2.4Vmin
1.8-5.5V
Electrode Array 64 pads
Evaluate 2 types of analog mux.
